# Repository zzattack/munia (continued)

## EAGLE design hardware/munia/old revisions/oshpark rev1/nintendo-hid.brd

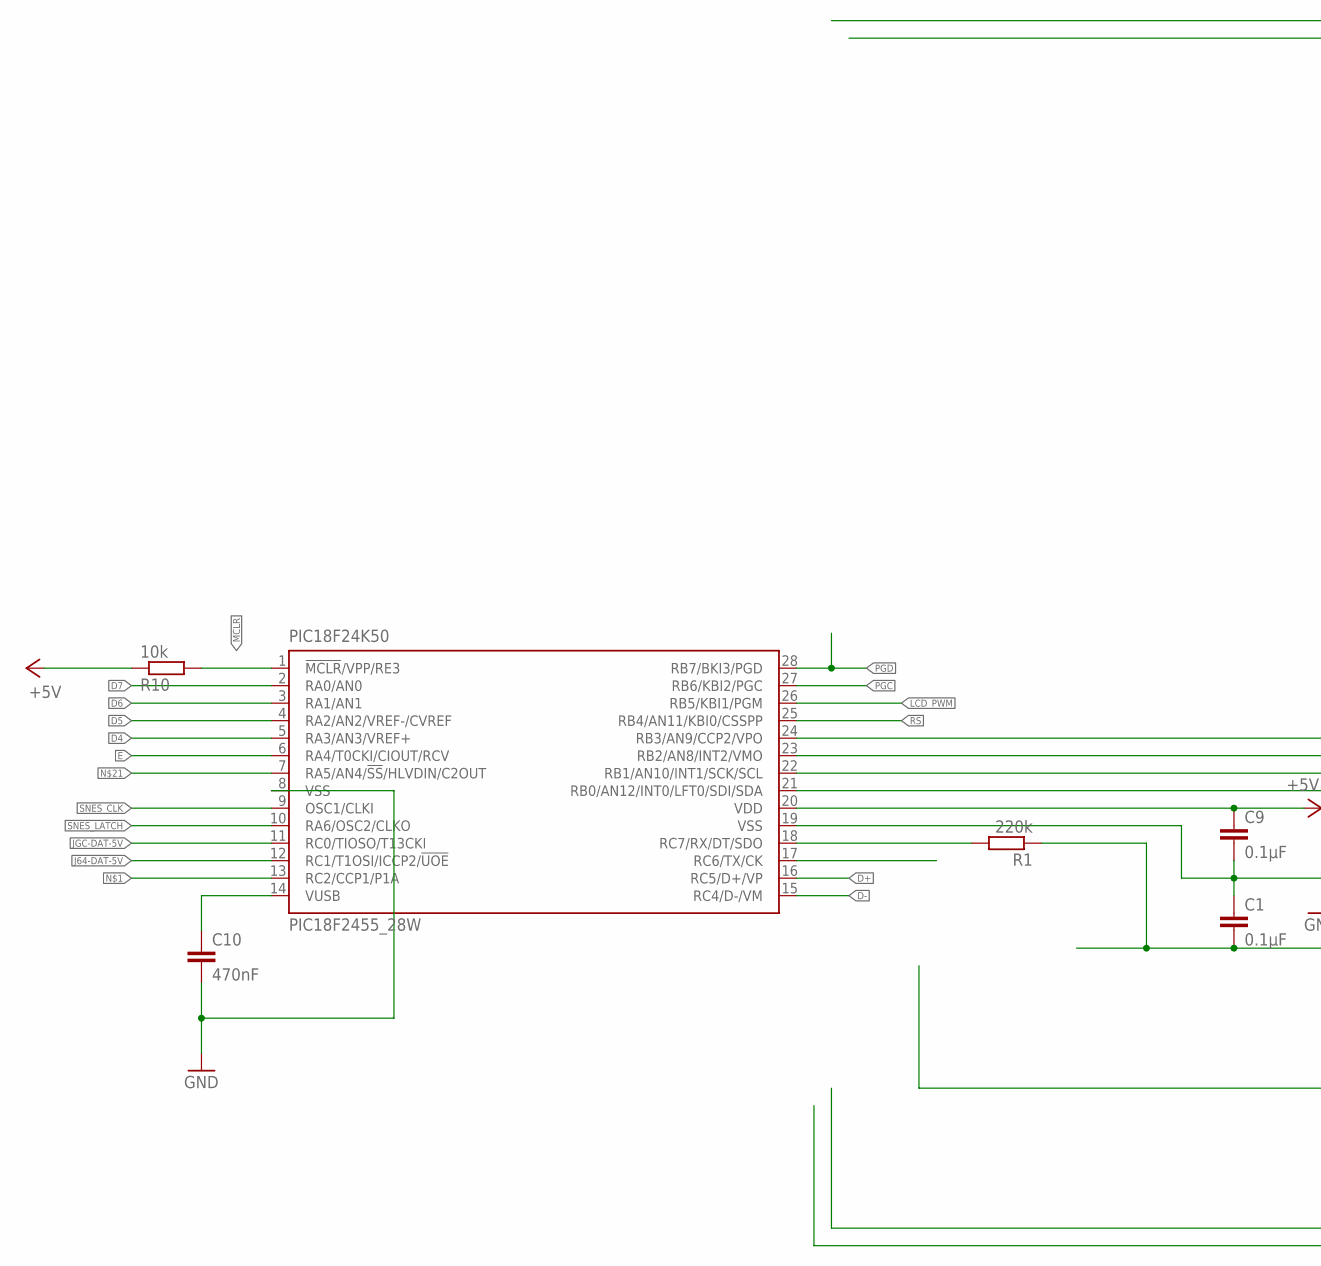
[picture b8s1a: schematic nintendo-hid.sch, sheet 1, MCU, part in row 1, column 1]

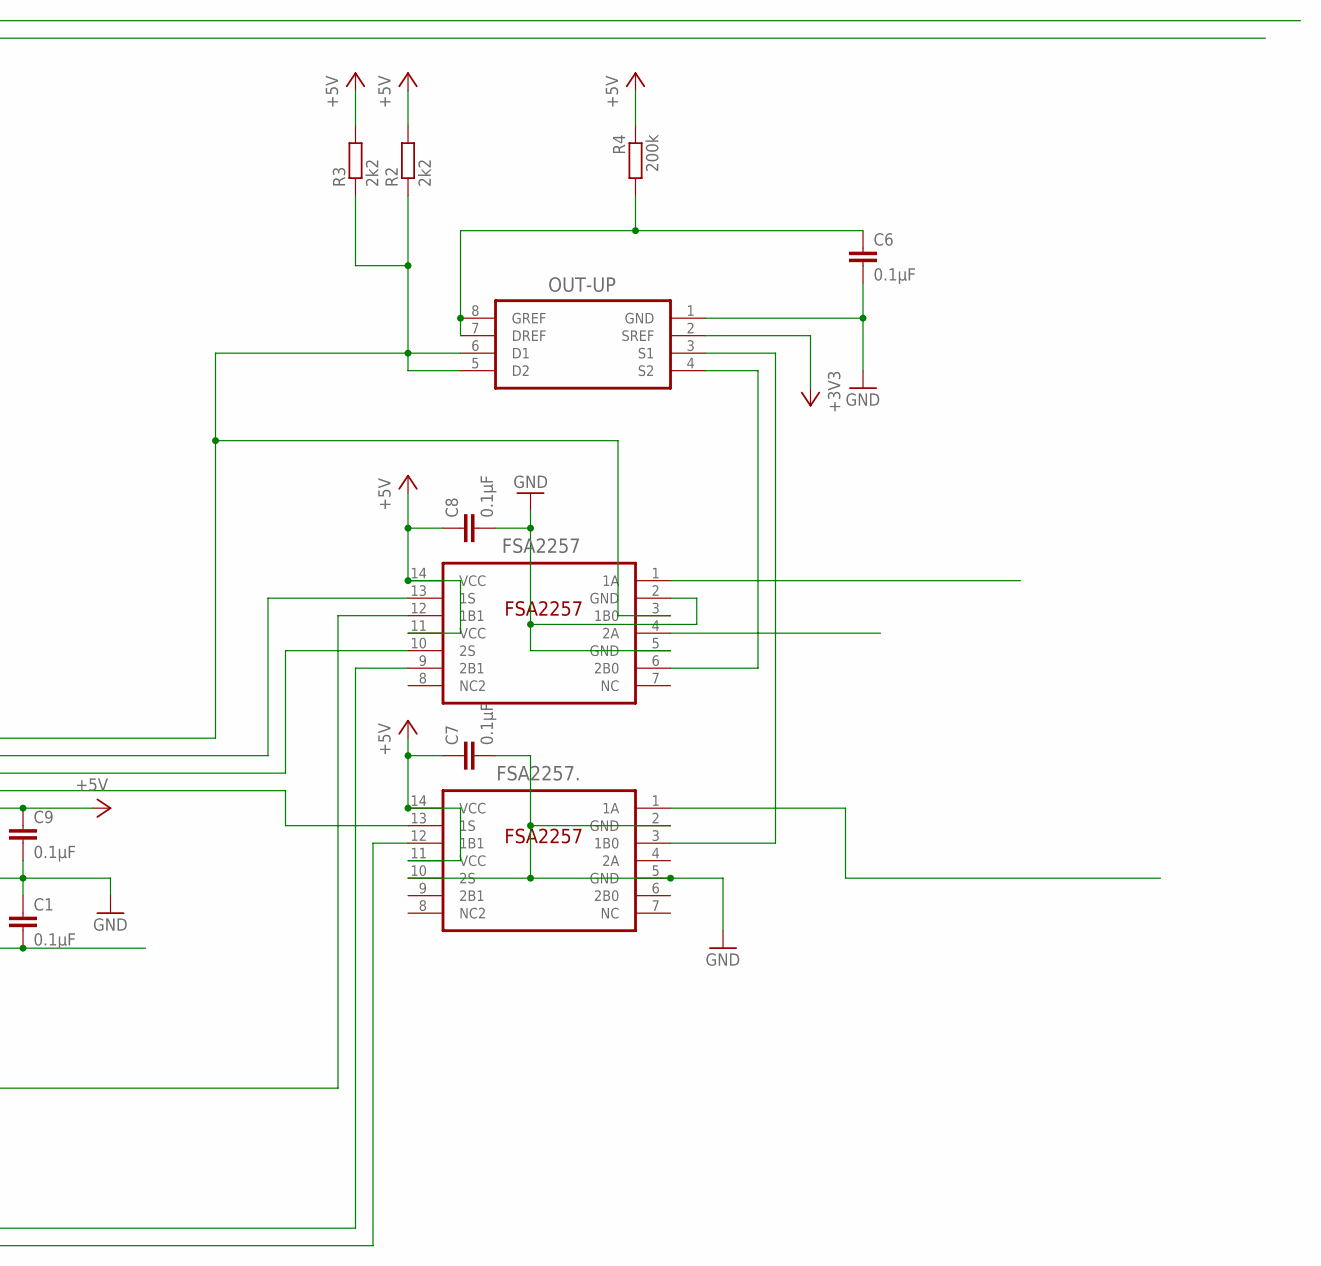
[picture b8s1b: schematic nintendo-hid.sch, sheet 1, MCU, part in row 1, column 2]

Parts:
C1, C6, C7, C8: 0.1µF; C0603
C9: 0.1µF; C0603K
C10: 470nF; C0603
FSA2257, FSA2257.: FSA2257MTCX; TSSOP14
OUT-UP: GTL2002D; SOIC127P600X175-8N
PIC18F24K50: PIC18F2455_28W; SO28W
R1: 220k; R0603
R2, R3: 2k2; R0603
R4: 200k; R0603
R10: 10k; R0603

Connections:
+3V3: OUT-UP.2 (SREF); also elsewhere on the board
+5V: C7.1, C8.1, C9.1, FSA2257.11 (VCC), FSA2257.14 (VCC), FSA2257..11 (VCC), FSA2257..14 (VCC), PIC18F24K50.20 (VDD), R2.2, R3.2, R4.1, R10.1; also elsewhere on the board
D4: PIC18F24K50.5 (RA3/AN3/VREF+); also elsewhere on the board
D5: PIC18F24K50.4 (RA2/AN2/VREF-/CVREF); also elsewhere on the board
D6: PIC18F24K50.3 (RA1/AN1); also elsewhere on the board
D7: PIC18F24K50.2 (RA0/AN0); also elsewhere on the board
D+: PIC18F24K50.16 (RC5/D+/VP); also elsewhere on the board
D-: PIC18F24K50.15 (RC4/D-/VM); also elsewhere on the board
E: PIC18F24K50.6 (RA4/T0CKI/CIOUT/RCV); also elsewhere on the board
FAKE_3V3.1: FSA2257.6 (2B0), OUT-UP.4 (S2)
FAKE_3V3.2: FSA2257..3 (1B0), OUT-UP.3 (S1)
FAKE_5V: FSA2257.3 (1B0), OUT-UP.5 (D2), OUT-UP.6 (D1), PIC18F24K50.24 (RB3/AN9/CCP2/VPO), R2.1, R3.1
GND: C1.1, C6.2, C7.2, C8.2, C9.2, C10.2, FSA2257.2 (GND), FSA2257.5 (GND), FSA2257..2 (GND), FSA2257..5 (GND), FSA2257..10 (2S), OUT-UP.1 (GND), PIC18F24K50.8 (VSS), PIC18F24K50.19 (VSS); also elsewhere on the board
J64-DAT-5V: PIC18F24K50.12 (RC1/T1OSI/ICCP2/!UOE)
J64_DAT: FSA2257.9 (2B1); also elsewhere on the board
JGC-DAT-5V: PIC18F24K50.11 (RC0/TIOSO/T13CKI)
JGC_DAT: FSA2257..12 (1B1); also elsewhere on the board
JSNES_DAT: FSA2257.12 (1B1)
LCD_PWM: PIC18F24K50.26 (RB5/KBI1/PGM); also elsewhere on the board
MCLR: PIC18F24K50.1 (!MCLR!/VPP/RE3), R10.2; also elsewhere on the board
unnamed 28: FSA2257.4 (2A); also elsewhere on the board
unnamed 34: FSA2257..1 (1A); also elsewhere on the board
unnamed: C10.1, PIC18F24K50.14 (VUSB)
unnamed: C6.1, OUT-UP.7 (DREF), OUT-UP.8 (GREF), R4.2
unnamed 41: PIC18F24K50.17 (RC6/TX/CK); also elsewhere on the board
PGC: PIC18F24K50.27 (RB6/KBI2/PGC); also elsewhere on the board
PGD: PIC18F24K50.28 (RB7/BKI3/PGD); also elsewhere on the board
RS: PIC18F24K50.25 (RB4/AN11/KBI0/CSSPP); also elsewhere on the board
S1: FSA2257.13 (1S), PIC18F24K50.23 (RB2/AN8/INT2/VMO)
S2: FSA2257.10 (2S), PIC18F24K50.22 (RB1/AN10/INT1/SCK/SCL)
S3: FSA2257..13 (1S), PIC18F24K50.21 (RB0/AN12/INT0/LFT0/SDI/SDA)
SNES_CLK: PIC18F24K50.9 (OSC1/CLKI); also elsewhere on the board
SNES_LATCH: PIC18F24K50.10 (RA6/OSC2/CLKO); also elsewhere on the board
SNES_OUT: FSA2257.1 (1A); also elsewhere on the board
USB-SENSE: PIC18F24K50.18 (RC7/RX/DT/SDO), R1.2
VBUS: C1.2, R1.1

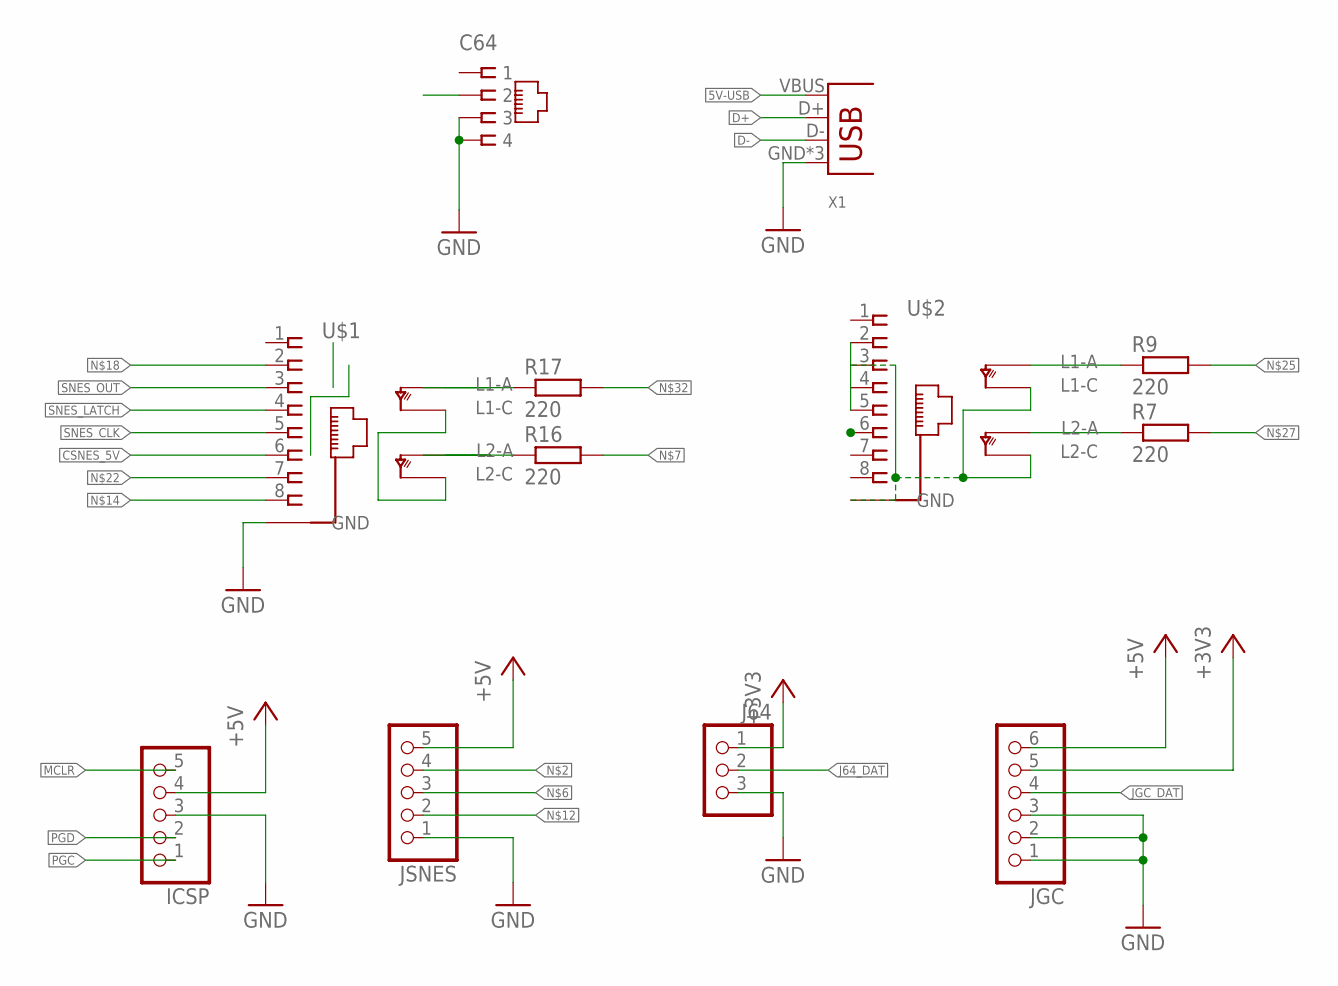
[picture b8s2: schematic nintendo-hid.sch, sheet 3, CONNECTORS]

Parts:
C64: RJ11-6P4C; RJ11-4C
ICSP: PINHD-1X5; 1X05
J64: PINHD-1X3; 1X03
JGC: PINHD-1X6; 1X06
JSNES: PINHD-1X5; 1X05
R7, R9, R16, R17: 220; R0603
U$1, U$2: RJ45-NIELS
X1: USB-B-NIELS; USB-B-H

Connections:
5V-USB: X1.VBUS; also elsewhere on the board
+3V3: J64.1, JGC.5; also elsewhere on the board
+5V: ICSP.4, JGC.6, JSNES.5; also elsewhere on the board
CSNES_5V: U$1.6
D+: X1.D+; also elsewhere on the board
D-: X1.D-; also elsewhere on the board
GND: C64.3, C64.4, ICSP.3, J64.3, JGC.1, JGC.2, JGC.3, JSNES.1, U$1.GND@5 (GND), U$1.GND@6 (GND), U$1.LED-GREEN-C (L2C), U$1.LED-ORANGE-C (L1C), U$2.2, U$2.3, U$2.4, U$2.5, U$2.GND@5 (GND), U$2.GND@6 (GND), U$2.LED-GREEN-C (L2C), U$2.LED-ORANGE-C (L1C), X1.GND, X1.GND@1 (GND), X1.GND@2 (GND); also elsewhere on the board
J64_DAT: J64.2; also elsewhere on the board
JGC_DAT: JGC.4; also elsewhere on the board
MCLR: ICSP.5; also elsewhere on the board
unnamed 28: C64.2; also elsewhere on the board
unnamed: R9.1, U$2.LED-ORANGE-A (L1A)
unnamed 34: U$2.6; also elsewhere on the board
unnamed 41: U$1.7; also elsewhere on the board
unnamed: R7.1, U$2.LED-GREEN-A (L2A)
PGC: ICSP.1; also elsewhere on the board
PGD: ICSP.2; also elsewhere on the board
SNES_CLK: U$1.5; also elsewhere on the board
SNES_LATCH: U$1.4; also elsewhere on the board
SNES_OUT: U$1.3; also elsewhere on the board

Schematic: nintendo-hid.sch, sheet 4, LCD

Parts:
BC547: BC547; TO92
LCD-DATA: PINHD-1X8; 1X08
LCD-PWR: PINHD-1X4; 1X04
R11: 1k; R0603
R12, R13: 20k; R0603

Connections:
+5V: LCD-DATA.2, LCD-PWR.2, R13.2; also elsewhere on the board
C: BC547.3 (C), LCD-DATA.1
D4: LCD-DATA.6; also elsewhere on the board
D5: LCD-DATA.5; also elsewhere on the board
D6: LCD-DATA.4; also elsewhere on the board
D7: LCD-DATA.3; also elsewhere on the board
E: LCD-DATA.7; also elsewhere on the board
GND: BC547.1 (E), LCD-DATA.8, LCD-PWR.1, R12.1; also elsewhere on the board
LCD_PWM: R11.2; also elsewhere on the board
unnamed: BC547.2 (B), R11.1
RS: LCD-PWR.4; also elsewhere on the board
VEE: LCD-PWR.3, R12.2, R13.1

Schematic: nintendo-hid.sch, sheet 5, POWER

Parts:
C2, C3: 0.1µF; C0603
D1, D2, D3: MBR120VLSFT1G; SOD123
U1: TC1262-3.3VDB; SOT230P700X180-4N

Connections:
5V-NGC: D3.2 (A)
5V-SNES: D2.2 (A)
5V-USB: D1.2 (A); also elsewhere on the board
+3V3: C3.1, U1.3 (OUT); also elsewhere on the board
+5V: C2.1, D1.1 (C), D2.1 (C), D3.1 (C), U1.1 (IN); also elsewhere on the board
GND: C2.2, C3.2, U1.2 (GND), U1.4 (GND); also elsewhere on the board

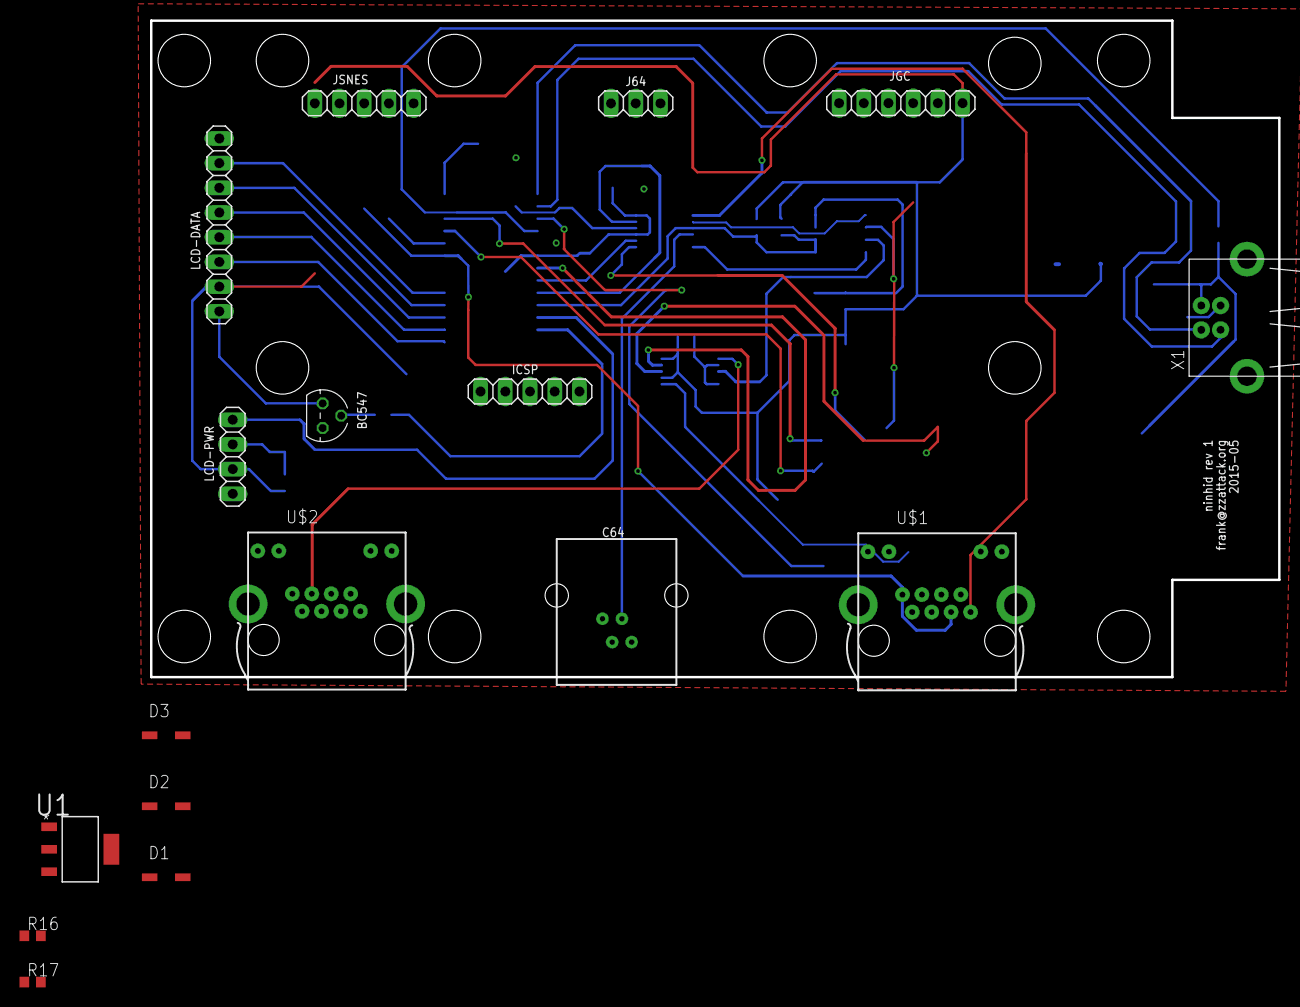
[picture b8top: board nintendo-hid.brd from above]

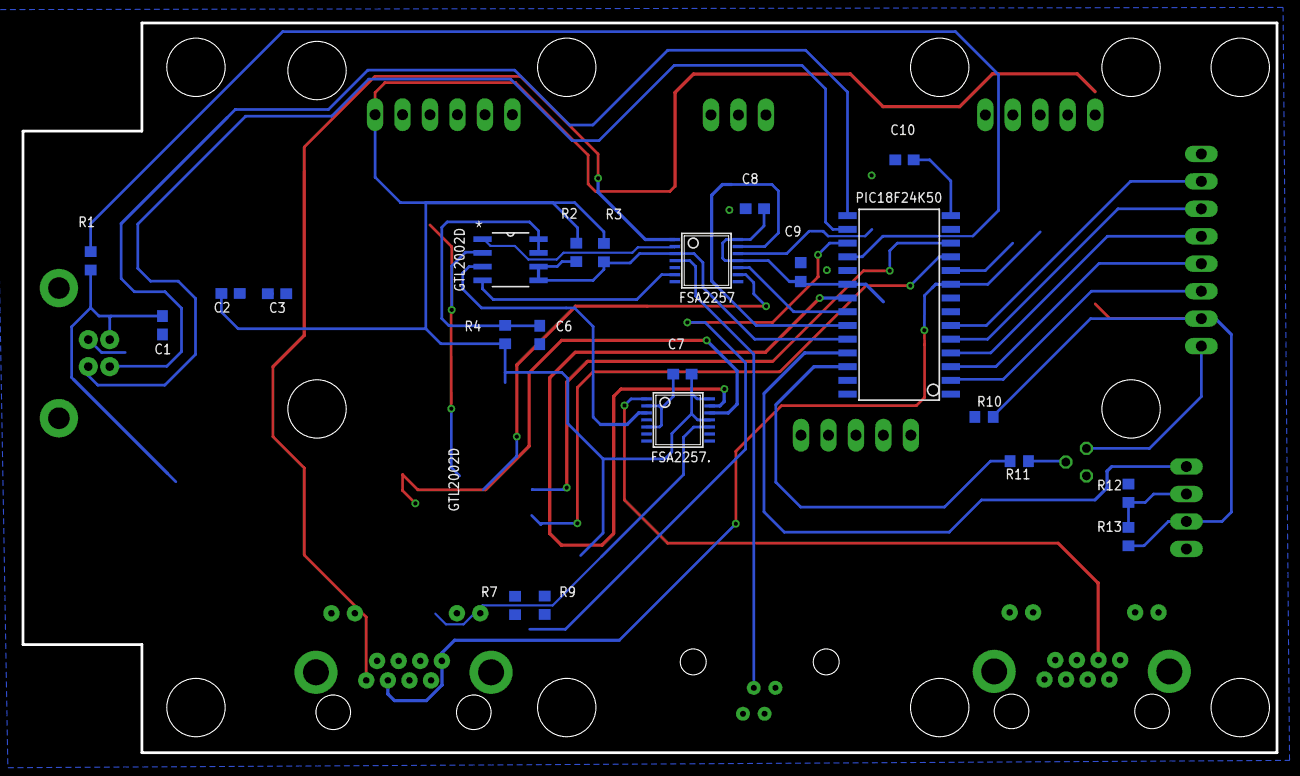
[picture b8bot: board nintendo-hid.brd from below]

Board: 2 copper layers, 116.0 x 67.5 mm, 39 parts (22 on the bottom side), 39 nets.

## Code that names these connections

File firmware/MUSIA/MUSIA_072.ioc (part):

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Mcu.Name=STM32F072C(8-B)Tx
Mcu.Package=LQFP48
Mcu.UserName=STM32F072CBTx
PA0.GPIOParameters=GPIO_Label,GPIO_ModeDefaultEXTI
PA0.GPIO_Label=JPS2_ATT
PA0.GPIO_ModeDefaultEXTI=GPIO_MODE_IT_RISING_FALLING
PA0.Signal=GPXTI0
PA1.GPIOParameters=GPIO_Label
PA1.GPIO_Label=JPS2_ACK
PA1.Signal=GPIO_Input
PA10.Mode=Asynchronous
PA10.Signal=USART1_RX
PA11.Mode=Device
PA11.Signal=USB_DM
PA12.Mode=Device
PA12.Signal=USB_DP
PA13.Mode=Serial_Wire
PA13.Signal=SYS_SWDIO
PA14.Mode=Serial_Wire
PA14.Signal=SYS_SWCLK
PA15.GPIOParameters=GPIO_Label
PA15.GPIO_Label=EE\#CS
PA15.Signal=GPIO_Output
PA2.GPIOParameters=GPIO_Label
PA2.GPIO_Label=LED1
PA2.Signal=GPIO_Output
PA3.GPIOParameters=GPIO_Label
PA3.GPIO_Label=LED2
PA3.Signal=GPIO_Output
PA4.GPIOParameters=GPIO_Label
PA4.GPIO_Label=LED3
PA4.Signal=GPIO_Output
PA5.Mode=Full_Duplex_Master
PA5.Signal=SPI1_SCK
PA6.Mode=Full_Duplex_Master
PA6.Signal=SPI1_MISO
PA7.Mode=Full_Duplex_Master
PA7.Signal=SPI1_MOSI
PA9.Mode=Asynchronous
PA9.Signal=USART1_TX
PB0.GPIOParameters=GPIO_Label
PB0.GPIO_Label=SW_CONSOLE_DISCONNECT
PB0.Signal=GPIO_Output
PB1.GPIOParameters=GPIO_Label
PB1.GPIO_Label=LED_ORANGE
PB1.Signal=GPIO_Output
PB10.Mode=Full_Duplex_Master
PB10.Signal=SPI2_SCK
PB12.GPIOParameters=GPIO_Label
PB12.GPIO_Label=SW_SNIFFER-CONSOLE
PB12.Signal=GPIO_Output
PB13.GPIOParameters=GPIO_Label
PB13.GPIO_Label=SW_PULLUP_ENABLE
PB13.Signal=GPIO_Output
PB14.Mode=Full_Duplex_Master
PB14.Signal=SPI2_MISO
PB15.Mode=Full_Duplex_Master
PB15.Signal=SPI2_MOSI
PB2.GPIOParameters=GPIO_Label
PB2.GPIO_Label=LED_GREEN
PB2.Signal=GPIO_Output
PB3.GPIOParameters=GPIO_Label
PB3.GPIO_Label=EE\#CS
PB3.Signal=GPIO_Output
PB9.GPIOParameters=GPIO_Label
PB9.GPIO_Label=SW_SPI_CLK
PB9.Signal=GPIO_Output
PC14-OSC32_IN.GPIOParameters=GPIO_Label
PC14-OSC32_IN.GPIO_Label=USB_VIBR_EN
PC14-OSC32_IN.Signal=GPIO_Output
PC15-OSC32_OUT.GPIOParameters=GPIO_Label
PC15-OSC32_OUT.GPIO_Label=PS2_VIBR_EN
PC15-OSC32_OUT.Signal=GPIO_Output
RCC.SYSCLKFreq_VALUE=32000000
RCC.SYSCLKSource=RCC_SYSCLKSOURCE_PLLCLK
board=custom

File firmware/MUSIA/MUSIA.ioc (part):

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Mcu.Name=STM32F042C(4-6)Tx
Mcu.Package=LQFP48
Mcu.UserName=STM32F042C4Tx
PA0.GPIOParameters=GPIO_Label,GPIO_ModeDefaultEXTI
PA0.GPIO_Label=JPS2_ATT
PA0.GPIO_ModeDefaultEXTI=GPIO_MODE_IT_RISING_FALLING
PA0.Signal=GPXTI0
PA1.GPIOParameters=GPIO_Label
PA1.GPIO_Label=JPS2_ACK
PA1.Signal=GPIO_Input
PA10.Mode=Asynchronous
PA10.Signal=USART1_RX
PA13.Mode=Serial_Wire
PA13.Signal=SYS_SWDIO
PA14.Mode=Serial_Wire
PA14.Signal=SYS_SWCLK
PA15.GPIOParameters=GPIO_Label
PA15.GPIO_Label=EE\#CS
PA15.Signal=GPIO_Output
PA2.GPIOParameters=PinState,GPIO_Label
PA2.GPIO_Label=LED1
PA2.PinState=GPIO_PIN_SET
PA2.Signal=GPIO_Output
PA3.GPIOParameters=PinState,GPIO_Label
PA3.GPIO_Label=LED2
PA3.PinState=GPIO_PIN_SET
PA3.Signal=GPIO_Output
PA4.GPIOParameters=PinState,GPIO_Label
PA4.GPIO_Label=LED3
PA4.PinState=GPIO_PIN_SET
PA4.Signal=GPIO_Output
PA9.Mode=Asynchronous
PA9.Signal=USART1_TX
PB0.GPIOParameters=GPIO_Speed,PinState,GPIO_Label
PB0.GPIO_Label=SW_CONSOLE_DISCONNECT
PB0.GPIO_Speed=GPIO_SPEED_FREQ_LOW
PB0.PinState=GPIO_PIN_RESET
PB0.Signal=GPIO_Output
PB1.GPIOParameters=GPIO_Label
PB1.GPIO_Label=LED_ORANGE
PB1.Signal=GPIO_Output
PB12.GPIOParameters=GPIO_Label
PB12.GPIO_Label=SW_SNIFFER-CONSOLE
PB12.Signal=GPIO_Output
PB13.GPIOParameters=GPIO_Label
PB13.GPIO_Label=SW_PULLUP_ENABLE
PB13.Signal=GPIO_Output
PB2.GPIOParameters=GPIO_Label
PB2.GPIO_Label=LED_GREEN
PB2.Signal=GPIO_Output
PB3.GPIOParameters=PinState,GPIO_Label,GPIO_ModeDefaultOutputPP
PB3.GPIO_Label=LCD_D7
PB3.GPIO_ModeDefaultOutputPP=GPIO_MODE_OUTPUT_PP
PB3.PinState=GPIO_PIN_RESET
PB3.Signal=GPIO_Output
PB4.GPIOParameters=PinState,GPIO_Label,GPIO_ModeDefaultOutputPP
PB4.GPIO_Label=LCD_D6
PB4.GPIO_ModeDefaultOutputPP=GPIO_MODE_OUTPUT_PP
PB4.PinState=GPIO_PIN_RESET
PB4.Signal=GPIO_Output
PB5.GPIOParameters=PinState,GPIO_Label,GPIO_ModeDefaultOutputPP
PB5.GPIO_Label=LCD_D5
PB5.GPIO_ModeDefaultOutputPP=GPIO_MODE_OUTPUT_PP
PB5.PinState=GPIO_PIN_RESET
PB5.Signal=GPIO_Output
PB6.GPIOParameters=PinState,GPIO_Label,GPIO_ModeDefaultOutputPP
PB6.GPIO_Label=LCD_D4
PB6.GPIO_ModeDefaultOutputPP=GPIO_MODE_OUTPUT_PP
PB6.PinState=GPIO_PIN_RESET
PB6.Signal=GPIO_Output
PB7.GPIOParameters=PinState,GPIO_Label,GPIO_ModeDefaultOutputPP
PB7.GPIO_Label=LCD_E
PB7.GPIO_ModeDefaultOutputPP=GPIO_MODE_OUTPUT_PP
PB7.PinState=GPIO_PIN_RESET
PB7.Signal=GPIO_Output
PB8.GPIOParameters=PinState,GPIO_Label,GPIO_ModeDefaultOutputPP
PB8.GPIO_Label=LCD_RS
PB8.GPIO_ModeDefaultOutputPP=GPIO_MODE_OUTPUT_PP
PB8.PinState=GPIO_PIN_RESET
PB8.Signal=GPIO_Output
PB9.GPIOParameters=PinState,GPIO_Label
PB9.GPIO_Label=SW_SPI_CLK
PB9.PinState=GPIO_PIN_SET
PB9.Signal=GPIO_Output
PC13.GPIOParameters=GPIO_Label
PC13.GPIO_Label=MENU_ALT
PC13.Signal=GPIO_Input
PC14OSC32_IN.GPIOParameters=GPIO_Speed,PinState,GPIO_PuPd,GPIO_Label,GPIO_ModeDefaultOutputPP
PC14OSC32_IN.GPIO_Label=LCD_PWM
PC14OSC32_IN.GPIO_ModeDefaultOutputPP=GPIO_MODE_OUTPUT_PP
PC14OSC32_IN.GPIO_PuPd=GPIO_PULLUP
PC14OSC32_IN.GPIO_Speed=GPIO_SPEED_FREQ_HIGH
PC14OSC32_IN.PinState=GPIO_PIN_RESET
PC14OSC32_IN.Signal=GPIO_Output
PC15OSC32_OUT.GPIOParameters=GPIO_Label
PC15OSC32_OUT.GPIO_Label=PS2_VIBR_EN
PC15OSC32_OUT.Signal=GPIO_Output
PF0-OSC_IN.Mode=HSE-External-Oscillator
PF0-OSC_IN.Signal=RCC_OSC_IN
PF1-OSC_OUT.Mode=HSE-External-Oscillator
PF1-OSC_OUT.Signal=RCC_OSC_OUT
PF11.GPIOParameters=GPIO_PuPd,GPIO_Label
PF11.GPIO_Label=MENU
PF11.GPIO_PuPd=GPIO_NOPULL
PF11.Signal=GPIO_Input
RCC.SYSCLKFreq_VALUE=48000000
RCC.SYSCLKSource=RCC_SYSCLKSOURCE_PLLCLK
board=custom

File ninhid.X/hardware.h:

#ifndef HARDWARE_H
#define	HARDWARE_H

#include <xc.h>
#include <stdint.h>

#define _XTAL_FREQ 48000000

#define SNES_DAT PORTCbits.RC2
#define SNES_LATCH PORTCbits.RC7
#define SNES_CLK PORTAbits.RA7
#define N64_DAT PORTCbits.RC1
#define NGC_DAT PORTCbits.RC0

#define SNES_DAT_TRIS TRISCbits.TRISC2
#define SNES_LATCH_TRIS TRISAbits.TRISA6
#define SNES_CLK_TRIS TRISAbits.TRISA7
#define N64_DAT_TRIS TRISCbits.TRISC1
#define NGC_DAT_TRIS TRISCbits.TRISC0

#define LED_SNES_GREEN LATAbits.LATA5
#define LED_SNES_ORANGE LATCbits.LATC6
#define LED_GC_GREEN LATBbits.LATB6
#define LED_GC_ORANGE LATBbits.LATB7

#define FAKE_DAT LATBbits.LATB3
#define SWITCH1 LATBbits.LATB2
#define SWITCH2 LATBbits.LATB1
#define SWITCH3 LATBbits.LATB0

#define LCD_RS LATBbits.LATB4
#define LCD_PWM LATBbits.LATB5
#define LCD_E LATAbits.LATA4
#define LCD_D4 LATAbits.LATA0
#define LCD_D5 LATAbits.LATA1
#define LCD_D6 LATAbits.LATA2
#define LCD_D7 LATAbits.LATA3

#define BUTTON_COUNT 1
#define BUTTON_0 BTN_MENU
#define BTN_MENU (!PORTEbits.RE3)
#define BTN_MENU_PRESSED bcPressed[0]

#endif	/* HARDWARE_H */

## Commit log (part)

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2018-06-24 missing files
    Former-commit-id: b55239398dae00ddfdb55c148e74e9d1562de1ad
2018-06-24 before regenerate
    Former-commit-id: 71b375cc0ff085a3c4122625cdf5e10611ae43e8
2018-06-24 reorganize
    Former-commit-id: ddc4bce0e5ae4cdae7f9ca02fd67ce2d1c6f22db
2018-06-24 working hid reports
    Former-commit-id: 11b8b478fc1b27c22a5acf8bca291bf26fe2da38
2018-06-25 convert to IntergatedCircuits usb stack
    Former-commit-id: 8296ccaa27c0cf9ff2b7c029842bef13cfde0bfc
2018-06-25 oops fix
    Former-commit-id: ab031829e728f522865cd564bd5fb51110469461
2018-06-25 ignore
    Former-commit-id: b8984731e2d4748ea7e918a742fa7138cbb17260
2018-06-25 license header crap
    Former-commit-id: b466db16439a13fb4537c49aa437e874ad350a2b
2018-06-25 remove traces of STM's USB stack
    Former-commit-id: 4ca9e43ab7999f90e73fb9982d99398442fa8fe8
2018-06-25 remove unused
    Former-commit-id: 026eeac60044ec74a0a22e124825a3ddcace87d4
2018-06-25 remove unused
    Former-commit-id: 3dc505025c755f5ef8e99269aa4b349135d7a6cb
2018-06-25 remove unused stuff
    Former-commit-id: 579f5097b3c20fba7ff95f5c2b66062b6db50ba8
2018-06-25 add schematics for all devices thus far
    Former-commit-id: 480aa2b86be94b459dd1aec146da21080f2f386a
2018-06-25 move
    Former-commit-id: 9f13b57de49d63ce73473e654a88a006a95b2b32
2018-06-25 remove irrelevant
    Former-commit-id: f357c1505c1af576f7d9beaf6eae50383b8965f0
2018-06-25 Create LICENSE
    Former-commit-id: 3a453772a451012e279af25f34f398dd2bdd04e0
2018-06-26 move cubemx stuff
    Former-commit-id: 3cb210831515f12b74933a74e59d7975454bf936
2018-06-26 organize USB folder
    Former-commit-id: 864fc584e5ec7eac6b4a1c7284ecfbec7fa89d2b
2018-06-26 regenerated
    Former-commit-id: 88d1dea33265e8d5df9d8f2860728a6df77472a6
2018-06-26 cleanup interfaces
    Former-commit-id: 75041042de2420765b50f102eaa3a62622d7ccee
2018-06-26 initial ps2 skin
    Former-commit-id: 2279bad70f26878d6a963ce25e88f8f53f64786b
2018-06-26 cleanup viewbox
    Former-commit-id: 164dfd3a013c7bd8d56d90d430e027bdf9c40ee9
2018-06-27 account for stroke width in object bounds calculation
    Former-commit-id: 5582309b945bd37c35f119a384eb8fe05f7926af
2018-06-27 add PS2 controller support
    Former-commit-id: b5e562b1621f6440d3f912c4bc517bde677bac0c
2018-06-27 save clean skins
    Former-commit-id: c852e0450f18157c2637f4945db2e74a23d4af89
2018-06-27 improve ps2 skin
    Former-commit-id: 02bdfd7aad1266a28bd20e2bb903c902ef09e40b
2018-06-27 remove .vs folder
    Former-commit-id: a3196effeb75bb6b159e0b5d95ede91fa01749f4
2018-06-27 enumeration bug fix
    Former-commit-id: ffc1755805c918a2ccbcdb8b9ead047a95a55653
2018-06-27 clock tune
    Former-commit-id: a5b1319f41d90ed9c1237a41936c7e7c1995cbf4
2018-06-27 HAL TIM inclusion
    Former-commit-id: 141a4c53bce6f873c56b0630f52c68f86eece83d
2018-06-27 expose HAL handle
    Former-commit-id: 2294e0707b199042071693f5a70c277d4adf6399
2018-06-27 configurator skeleton
    Former-commit-id: 0b4bd0eb696caca5210bbb76258e9290385e61d4
2018-06-27 poller framework
    Former-commit-id: 37f74f04a5b11642b713be8cc82be120cf0c7d93
2018-06-27 project mgmnt
    Former-commit-id: d145ae75aadc889baa53e2c02c398e248564d143
2018-06-27 ee layout
    Former-commit-id: 32e45005a684f8d3decc9a62683d03cdb8bdba25
2018-06-27 cleanup unused
    Former-commit-id: 9fe5228de291d181e03746c6ea6a36b2619ea711
2018-06-27 debug print stub
    Former-commit-id: 94055ad8a00939abb7dcdb9b17b9c753172f6a04
2018-06-27 this is where sniffer still works
    Former-commit-id: d445251ccdb4abc907ca7c2e9df5767234f38de7
2018-06-27 remove pics
2018-06-27 fix spi init sequence
2018-06-27 hardfault print message
2018-06-27 call signature fix
2018-06-27 packet definition shared by poller and sniffer
2018-06-27 fail-safe GPIO init values
2018-06-27 sync
2018-06-27 eeprom status logging
2018-06-29 bootloader entry mechanism
2018-06-29 form center parent positioning
2018-06-29 log spam reduce
2018-06-29 remove unused
2018-06-29 multi-device and ps2 device support
2018-07-01 update for deprecated hidsharp functions
2018-07-01 undo test thingie
2018-07-01 break on hardfault
2018-07-01 we're not self-powered
2018-07-01 fix possible buffer overflow after interrupted sniffing DMA
2018-07-01 improve polling reliability
2018-07-01 different bootloader image location depending on MCU
2018-07-01 make XPD use the correct mcu include
2018-07-01 rename
2018-07-01 project files updated
2018-07-02 Update SKINS.md
    info w.r.t. pressable sticks
2018-07-04 blinkie
2018-07-04 cleanup
2018-07-10 apply USB lib patches a8a1aa24, 9a37195f, 7dceef3e, cbd62e59
2018-07-11 remove USB vibration idea
2018-07-11 correct MSBuild.exe path
2018-07-11 beginning of skin remapping UI
2018-07-11 missing file
2018-07-11 remove force-feedback stuff
2018-07-11 remvoe report ids
2018-07-11 remove rumble, report id check
2018-07-12 apply ae568638 from IntergatedCircuits/USBDevice
2018-07-12 reapply my patches
2018-07-12 move skin-related code file to MUNIA.Skinning
2018-07-12 convert to usercontrol
2018-07-12 remap persistence
2018-07-12 color to hex string (ColorTranslator tends to pick non-hex names when possible)
2018-07-12 remap manager completed
2018-07-12 usings
2018-07-12 start updating controller already in the background
2018-07-12 change callback signature for fixed USB lib
2018-07-12 rename compact skin to digital
2018-07-12 compare by ARGB value
2018-07-12 store Fill & Stroke inside group
2018-07-12 click-to-activate color modes
2018-07-12 skin folder manager
2018-07-12 remapper improvements
2018-07-12 double click event in list
2018-07-12 option to disable flashing, prevent backlog in rendering
2018-07-12 tab infos
2018-07-14 revert to old HidDeviceLoader
2018-07-14 mini fix
2018-07-14 reworded
2018-07-14 version bump
2018-07-14 remvoe ff files
2018-07-14 LCD pins
2018-07-14 remove printf from debug
2018-07-14 deviceid stuff
2018-07-14 schedule polling quickly after packet sent
2018-07-15 remove unused include
2018-07-16 munia-n64 project
2018-07-16 randomized device id
2018-07-16 add menu & LCD
2018-07-16 menu alt pin
2018-07-16 lcd backlight for menu
2018-07-17 remove old theme stuff
2018-07-17 remove console modes and repro carts sections
2018-07-17 remove unused tests
2018-07-17 update ignores
2018-07-17 updated settings_dev, old apps removed, munia_io.db as sqlite name
2018-07-17 minifix when no remap selected
2018-07-17 improve config menu
2018-07-17 project build properties
2018-07-17 typo correction
2018-07-17 add static contents
2018-07-17 faq css/js
2018-07-17 this shouldn't be here
2018-07-18 remap engine image
2018-07-18 fix ignore
2018-07-18 devices page
2018-07-18 placeholder image
2018-07-31 fix faq on mobile
2018-07-31 add success page
2018-07-31 buynow button
2018-08-01 payment buttons
2018-08-01 no favico
2018-08-01 contact form
2018-08-01 will email
2018-08-01 use vs2017 build tools
2018-08-01 buy button on main page
2018-08-02 z-index missing on snes non-pressed buttons
2018-08-02 bounds fix
2018-08-02 version stuff
2018-08-03 add slick
2018-08-03 slick css
2018-08-03 slick static stuff
2018-08-03 add software page
2018-08-03 link fix
2018-08-03 url fix
2018-08-04 remove adapters app
2018-08-04 add analytical stub
2018-08-07 optional padding stuff
2018-08-08 improve psacing
2018-08-08 more padding fix
2018-08-12 regenerate
2018-08-12 LCD/poller ifdefs
2018-08-12 debug logging
2018-08-14 download button
2018-08-14 remove unnecessary printf
2018-08-14 optional printf_payload
2018-08-14 xc8 1.44 --> 1.45
2018-08-14 auto version thing
2018-08-14 readonlys
2018-09-29 debug print fix
2018-09-29 set correct PIC18 LF device
2018-09-29 update usbd_config.h from template
2018-09-29 usb lib fix?
2018-10-15 stash
2018-11-04 new cable type
2018-11-04 initial real support for nintendospy skins
2018-11-21 don't break on non-existing directories
2018-11-21 minor refactor
2018-11-21 placeholder for new controller types
2018-11-21 Bump version
2018-11-24 add support for a generic kind of HID gamepad, using HidSharp's report parsing capabilities
2018-11-24 update OpenTK and HidSharp packages
2018-11-24 changed name after OpenTK update
2018-11-25 add missing skins
2018-11-25 correct axis mapping to match directinput
2018-11-25 correct case
2018-11-25 reattach event handlers
2018-11-25 fixes from pull requests
2018-11-25 fast skin preview from menu
2018-11-25 define IsTrigger test for known controllers
2018-11-25 fix hat behavior when logical minimum is not set to 0
2018-11-25 more aggressive closing of skin preview
2018-11-25 add x360 icon for generic controllers
2018-11-25 paint a visual representation of controller state instead of strings on canvas
2018-11-26 load/unload padpyght bitmaps/textures upon activation/deactivation to speed up skins loading
2018-11-26 use WorkingDir path combinatiation similar to nspy skins
2018-11-26 remove TODO
2018-11-26 add IsAxisTrigger lookup method on controller interface
2018-11-26 perform initial drawing using controller state at time of activation
2018-11-28 add support for XInput controllers
2018-11-28 render to requested size
2018-11-28 polling controller, needed for periodically checking XInput controller state
2018-11-28 remove usings
2018-11-28 make description panel optional
2018-12-01 add xbox one skin
2018-12-01 embed thextera's orange theme
2018-12-01 improve mapping stuff
2018-12-01 improve controller mapping process
2018-12-02 combine different color schemes into embedded remaps
2018-12-02 define built-in mappings for XInput controller
2018-12-02 use DefaultIfEmpty with MinValue i.c.m. sequence Max
2018-12-02 use but don't save built in mappings
2018-12-02 minor reorganize
2018-12-02 detect deactivation
2018-12-02 distinguish built-in and user-defined mappings
2018-12-03 complete UI for defining mappings
2018-12-03 mapper ui improvements
2018-12-12 allow unsafe also in release build (for crc32)
2018-12-24 fix invalid attribute
2018-12-24 since IsAvailable is now used for menu filtering, make sure its result is correct
2018-12-24 rangebuttons apply over axes, not buttons
2018-12-24 add button to set window size to skin default
2019-01-26 axis value shown next to bar in controller tester forms
2019-02-12 some corrections for trigger/axis mapping
2019-02-12 use re_path for urls
2019-02-12 make urls really reversible
2019-02-12 rename GetNumberOfElements -> GetMaxElementNumber because that's what it does
2019-02-12 be even less restrictive
2019-03-16 update usb lib with backported changes
2019-03-25 Correctly activate controller on app load (went wrong with mapped+buffered)
2019-03-31 improve PS1 robustness
2019-03-31 pinswap firmware
2019-04-17 don't crash on invalid arduino controller type
2019-04-28 ignores
2019-04-28 update project
2019-05-20 Support MUSIA controllers that report pressure sensor values
2019-05-20 add missing release config
2019-05-20 fix pressure sensor count to 12
2020-02-17 make compatible with latest django
2020-06-26 update rev2 with power from console
2020-06-26 Add missing printf-stdarg files
2020-06-26 Replace html contact form with a django form including recaptcha
2020-12-13 fix dpad button assignments for xbone skin
2020-12-13 fix exception on very first run when skins themes folder does not yet exist
2020-12-13 updat build script for vs2019
